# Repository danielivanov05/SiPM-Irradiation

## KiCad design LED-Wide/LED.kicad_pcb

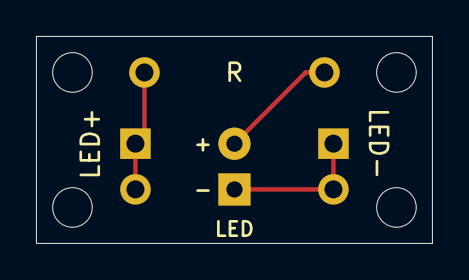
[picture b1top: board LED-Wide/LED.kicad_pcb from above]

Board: 2 copper layers, 22.0 x 11.5 mm, 4 parts (0 on the bottom side), 3 nets.

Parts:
LED: LED; LED_D5.0mm
LED+: Conn_01x02_Pin; PinHeader_1x02_P2.54mm_Vertical
LED-: Conn_01x02_Pin; PinHeader_1x02_P2.54mm_Vertical
R: R; Custom_PinHeader_1x02_P2.54mm_Vertical_Spaced_10mm

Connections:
LED+: LED+.1, LED+.2, R.1
LED-: LED.1 (K), LED-.1, LED-.2
unnamed: LED.2 (A), R.2

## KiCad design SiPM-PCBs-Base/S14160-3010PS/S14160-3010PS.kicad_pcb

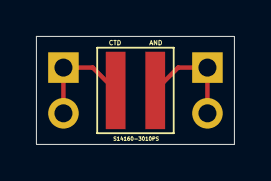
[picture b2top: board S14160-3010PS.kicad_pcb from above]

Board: 2 copper layers, 11.0 x 6.0 mm, 3 parts (0 on the bottom side), 2 nets.

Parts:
D1: S14160-3010PS
J-PWR-2: Conn_01x02_Pin; Custom_PinHeader_1x02_P2.54mm_Vertical
J-SIG-2: Conn_01x02_Pin; Custom_PinHeader_1x02_P2.54mm_Vertical

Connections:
HV+: D1.1 (K-), J-PWR-2.1, J-PWR-2.2
SIG: D1.2 (A+), J-SIG-2.1, J-SIG-2.2

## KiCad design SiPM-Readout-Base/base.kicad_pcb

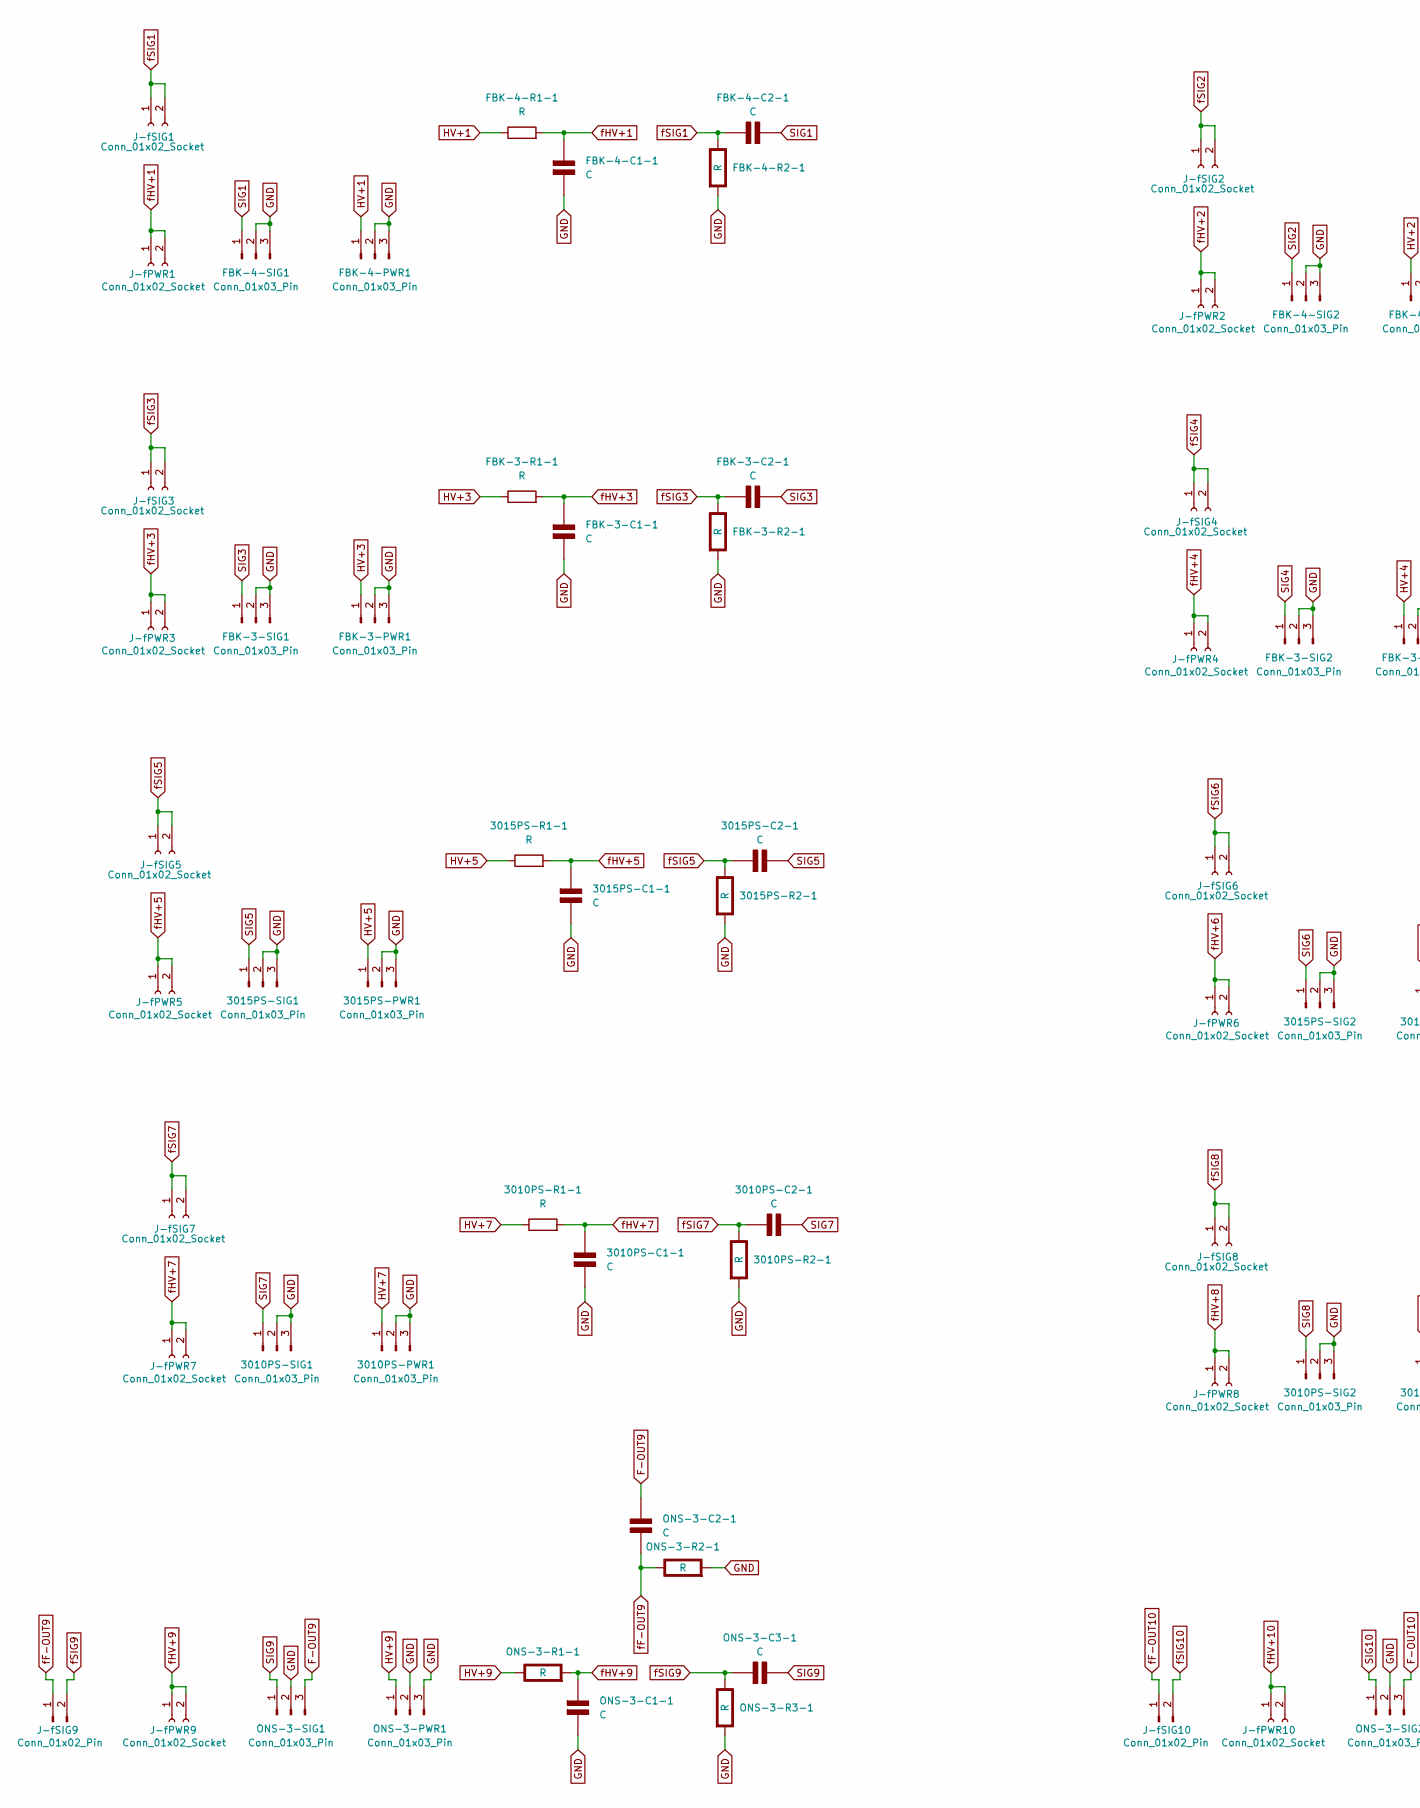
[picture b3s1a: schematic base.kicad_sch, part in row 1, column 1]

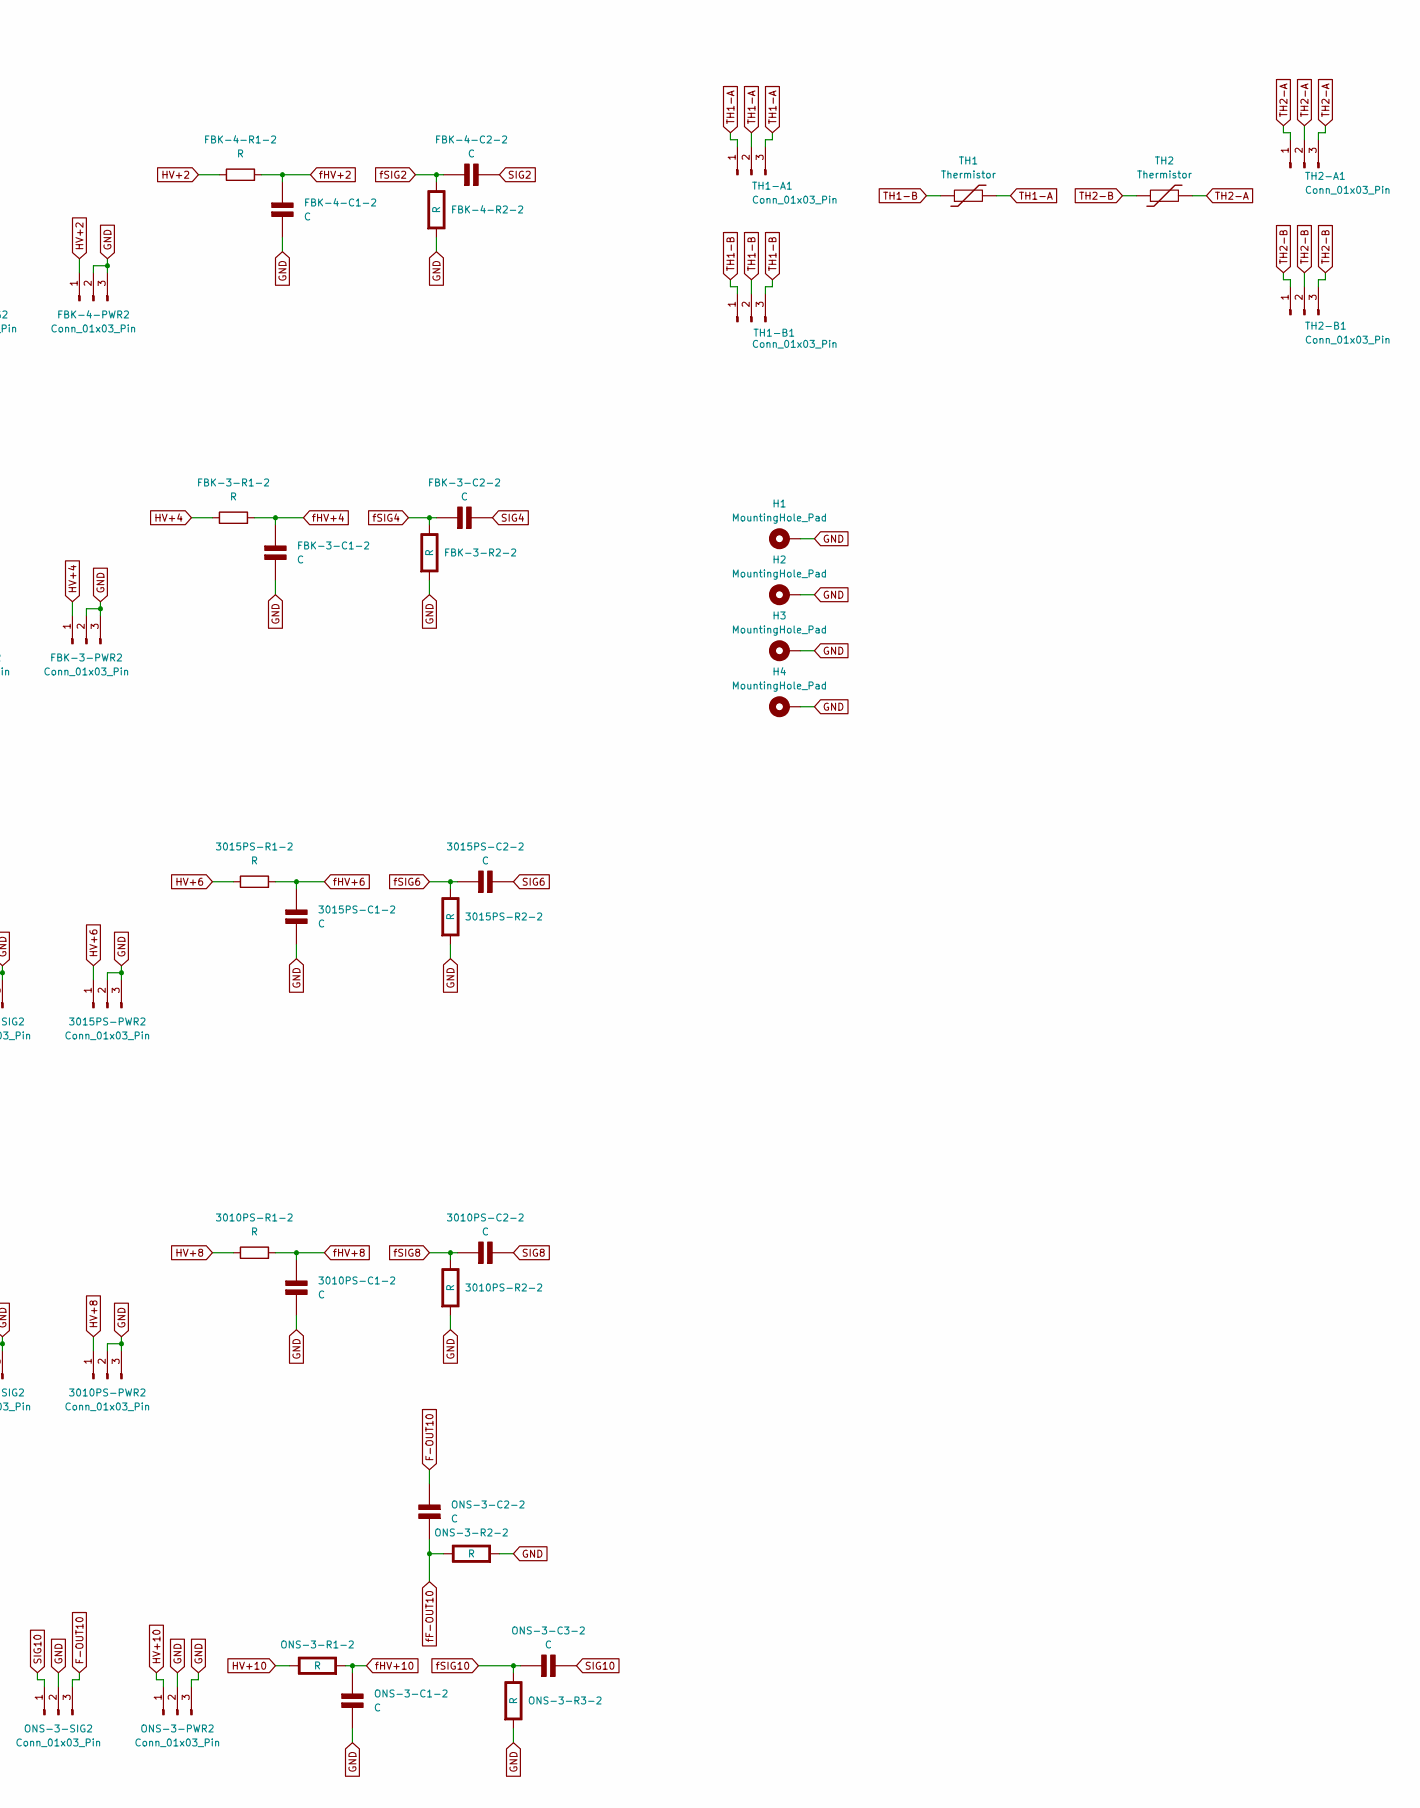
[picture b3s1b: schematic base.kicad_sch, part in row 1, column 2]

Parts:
3010PS-C1-1, 3010PS-C1-2, 3010PS-C2-1, 3010PS-C2-2, 3015PS-C1-1, 3015PS-C1-2, 3015PS-C2-1, 3015PS-C2-2: C; Custom_PinHeader_1x02_P2.54mm_Vertical_Spaced_10mm; Rating V
3010PS-PWR1, 3010PS-PWR2, 3010PS-SIG1, 3010PS-SIG2, 3015PS-PWR1, 3015PS-PWR2, 3015PS-SIG1, 3015PS-SIG2: Conn_01x03_Pin; PinHeader_1x03_P2.54mm_Vertical
3010PS-R1-1, 3010PS-R1-2, 3015PS-R1-1, 3015PS-R1-2: R; Custom_PinHeader_1x02_P2.54mm_Vertical_Spaced_10mm; Rating V
3010PS-R2-1, 3010PS-R2-2, 3015PS-R2-1, 3015PS-R2-2: R; Custom_PinHeader_1x02_P2.54mm_Vertical_Spaced_10mm; Rating W
FBK-3-C1-1, FBK-3-C1-2, FBK-3-C2-1, FBK-3-C2-2, FBK-4-C1-1, FBK-4-C1-2, FBK-4-C2-1, FBK-4-C2-2: C; Custom_PinHeader_1x02_P2.54mm_Vertical_Spaced_10mm; Rating V
FBK-3-PWR1, FBK-3-PWR2, FBK-3-SIG1, FBK-3-SIG2, FBK-4-PWR1, FBK-4-PWR2, FBK-4-SIG1, FBK-4-SIG2: Conn_01x03_Pin; PinHeader_1x03_P2.54mm_Vertical
FBK-3-R1-1, FBK-3-R1-2, FBK-4-R1-1, FBK-4-R1-2: R; Custom_PinHeader_1x02_P2.54mm_Vertical_Spaced_10mm; Rating V
FBK-3-R2-1, FBK-3-R2-2, FBK-4-R2-1, FBK-4-R2-2: R; Custom_PinHeader_1x02_P2.54mm_Vertical_Spaced_10mm; Rating W
H1, H2, H3, H4: MountingHole_Pad; MountingHole_2.2mm_M2_DIN965_Pad_TopBottom
J-fPWR1, J-fPWR2, J-fPWR3, J-fPWR4, J-fPWR5, J-fPWR6, J-fPWR7, J-fPWR8, J-fPWR9, J-fPWR10: Conn_01x02_Socket; Custom_PCB-Sized_PinSocket_1x02_P2.54mm_Vertical
J-fSIG1, J-fSIG2, J-fSIG3, J-fSIG4, J-fSIG5, J-fSIG6, J-fSIG7, J-fSIG8: Conn_01x02_Socket; No_Courtyard_PinSocket_1x02_P2.54mm_Vertical
J-fSIG9, J-fSIG10: Conn_01x02_Pin; No_Courtyard_PinSocket_1x02_P2.54mm_Vertical
ONS-3-C1-1, ONS-3-C1-2, ONS-3-C2-1, ONS-3-C2-2, ONS-3-C3-1, ONS-3-C3-2: C; Custom_PinHeader_1x02_P2.54mm_Vertical_Spaced_10mm; Rating V
ONS-3-PWR1, ONS-3-PWR2, ONS-3-SIG1, ONS-3-SIG2: Conn_01x03_Pin; PinHeader_1x03_P2.54mm_Vertical
ONS-3-R1-1, ONS-3-R1-2, ONS-3-R2-1, ONS-3-R2-2, ONS-3-R3-1, ONS-3-R3-2: R; Custom_PinHeader_1x02_P2.54mm_Vertical_Spaced_10mm; Rating W
TH1, TH2: Thermistor; Custom_PinHeader_1x02_P2.54mm_Vertical_Spaced_10mm
TH1-A1, TH1-B1, TH2-A1, TH2-B1: Conn_01x03_Pin; PinHeader_1x03_P2.54mm_Vertical

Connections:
F-OUT9: ONS-3-C2-1.2 (-), ONS-3-SIG1.3
F-OUT10: ONS-3-C2-2.2 (-), ONS-3-SIG2.3
GND: 3010PS-C1-1.2 (-), 3010PS-C1-2.2 (-), 3010PS-PWR1.2, 3010PS-PWR1.3, 3010PS-PWR2.2, 3010PS-PWR2.3, 3010PS-R2-1.2 (-), 3010PS-R2-2.2 (-), 3010PS-SIG1.2, 3010PS-SIG1.3, 3010PS-SIG2.2, 3010PS-SIG2.3, 3015PS-C1-1.2 (-), 3015PS-C1-2.2 (-), 3015PS-PWR1.2, 3015PS-PWR1.3, 3015PS-PWR2.2, 3015PS-PWR2.3, 3015PS-R2-1.2 (-), 3015PS-R2-2.2 (-), 3015PS-SIG1.2, 3015PS-SIG1.3, 3015PS-SIG2.2, 3015PS-SIG2.3, FBK-3-C1-1.2 (-), FBK-3-C1-2.2 (-), FBK-3-PWR1.2, FBK-3-PWR1.3, FBK-3-PWR2.2, FBK-3-PWR2.3, FBK-3-R2-1.2 (-), FBK-3-R2-2.2 (-), FBK-3-SIG1.2, FBK-3-SIG1.3, FBK-3-SIG2.2, FBK-3-SIG2.3, FBK-4-C1-1.2 (-), FBK-4-C1-2.2 (-), FBK-4-PWR1.2, FBK-4-PWR1.3, FBK-4-PWR2.2, FBK-4-PWR2.3, FBK-4-R2-1.2 (-), FBK-4-R2-2.2 (-), FBK-4-SIG1.2, FBK-4-SIG1.3, FBK-4-SIG2.2, FBK-4-SIG2.3, H1.1, H2.1, H3.1, H4.1, ONS-3-C1-1.2 (-), ONS-3-C1-2.2 (-), ONS-3-PWR1.2, ONS-3-PWR1.3, ONS-3-PWR2.2, ONS-3-PWR2.3, ONS-3-R2-1.2 (-), ONS-3-R2-2.2 (-), ONS-3-R3-1.2 (-), ONS-3-R3-2.2 (-), ONS-3-SIG1.2, ONS-3-SIG2.2
HV+1: FBK-4-PWR1.1, FBK-4-R1-1.1
HV+2: FBK-4-PWR2.1, FBK-4-R1-2.1
HV+3: FBK-3-PWR1.1, FBK-3-R1-1.1
HV+4: FBK-3-PWR2.1, FBK-3-R1-2.1
HV+5: 3015PS-PWR1.1, 3015PS-R1-1.1
HV+6: 3015PS-PWR2.1, 3015PS-R1-2.1
HV+7: 3010PS-PWR1.1, 3010PS-R1-1.1
HV+8: 3010PS-PWR2.1, 3010PS-R1-2.1
HV+9: ONS-3-PWR1.1, ONS-3-R1-1.1 (+)
HV+10: ONS-3-PWR2.1, ONS-3-R1-2.1 (+)
SIG1: FBK-4-C2-1.2 (-), FBK-4-SIG1.1
SIG2: FBK-4-C2-2.2 (-), FBK-4-SIG2.1
SIG3: FBK-3-C2-1.2 (-), FBK-3-SIG1.1
SIG4: FBK-3-C2-2.2 (-), FBK-3-SIG2.1
SIG5: 3015PS-C2-1.2 (-), 3015PS-SIG1.1
SIG6: 3015PS-C2-2.2 (-), 3015PS-SIG2.1
SIG7: 3010PS-C2-1.2 (-), 3010PS-SIG1.1
SIG8: 3010PS-C2-2.2 (-), 3010PS-SIG2.1
SIG9: ONS-3-C3-1.2 (-), ONS-3-SIG1.1
SIG10: ONS-3-C3-2.2 (-), ONS-3-SIG2.1
TH1-A: TH1.2, TH1-A1.1, TH1-A1.2, TH1-A1.3
TH1-B: TH1.1, TH1-B1.1, TH1-B1.2, TH1-B1.3
TH2-A: TH2.2, TH2-A1.1, TH2-A1.2, TH2-A1.3
TH2-B: TH2.1, TH2-B1.1, TH2-B1.2, TH2-B1.3
fF-OUT9: J-fSIG9.1, ONS-3-C2-1.1 (+), ONS-3-R2-1.1 (+)
fF-OUT10: J-fSIG10.1, ONS-3-C2-2.1 (+), ONS-3-R2-2.1 (+)
fHV+1: FBK-4-C1-1.1 (+), FBK-4-R1-1.2, J-fPWR1.1, J-fPWR1.2
fHV+2: FBK-4-C1-2.1 (+), FBK-4-R1-2.2, J-fPWR2.1, J-fPWR2.2
fHV+3: FBK-3-C1-1.1 (+), FBK-3-R1-1.2, J-fPWR3.1, J-fPWR3.2
fHV+4: FBK-3-C1-2.1 (+), FBK-3-R1-2.2, J-fPWR4.1, J-fPWR4.2
fHV+5: 3015PS-C1-1.1 (+), 3015PS-R1-1.2, J-fPWR5.1, J-fPWR5.2
fHV+6: 3015PS-C1-2.1 (+), 3015PS-R1-2.2, J-fPWR6.1, J-fPWR6.2
fHV+7: 3010PS-C1-1.1 (+), 3010PS-R1-1.2, J-fPWR7.1, J-fPWR7.2
fHV+8: 3010PS-C1-2.1 (+), 3010PS-R1-2.2, J-fPWR8.1, J-fPWR8.2
fHV+9: J-fPWR9.1, J-fPWR9.2, ONS-3-C1-1.1 (+), ONS-3-R1-1.2 (-)
fHV+10: J-fPWR10.1, J-fPWR10.2, ONS-3-C1-2.1 (+), ONS-3-R1-2.2 (-)
fSIG1: FBK-4-C2-1.1 (+), FBK-4-R2-1.1 (+), J-fSIG1.1, J-fSIG1.2
fSIG2: FBK-4-C2-2.1 (+), FBK-4-R2-2.1 (+), J-fSIG2.1, J-fSIG2.2
fSIG3: FBK-3-C2-1.1 (+), FBK-3-R2-1.1 (+), J-fSIG3.1, J-fSIG3.2
fSIG4: FBK-3-C2-2.1 (+), FBK-3-R2-2.1 (+), J-fSIG4.1, J-fSIG4.2
fSIG5: 3015PS-C2-1.1 (+), 3015PS-R2-1.1 (+), J-fSIG5.1, J-fSIG5.2
fSIG6: 3015PS-C2-2.1 (+), 3015PS-R2-2.1 (+), J-fSIG6.1, J-fSIG6.2
fSIG7: 3010PS-C2-1.1 (+), 3010PS-R2-1.1 (+), J-fSIG7.1, J-fSIG7.2
fSIG8: 3010PS-C2-2.1 (+), 3010PS-R2-2.1 (+), J-fSIG8.1, J-fSIG8.2
fSIG9: J-fSIG9.2, ONS-3-C3-1.1 (+), ONS-3-R3-1.1 (+)
fSIG10: J-fSIG10.2, ONS-3-C3-2.1 (+), ONS-3-R3-2.1 (+)

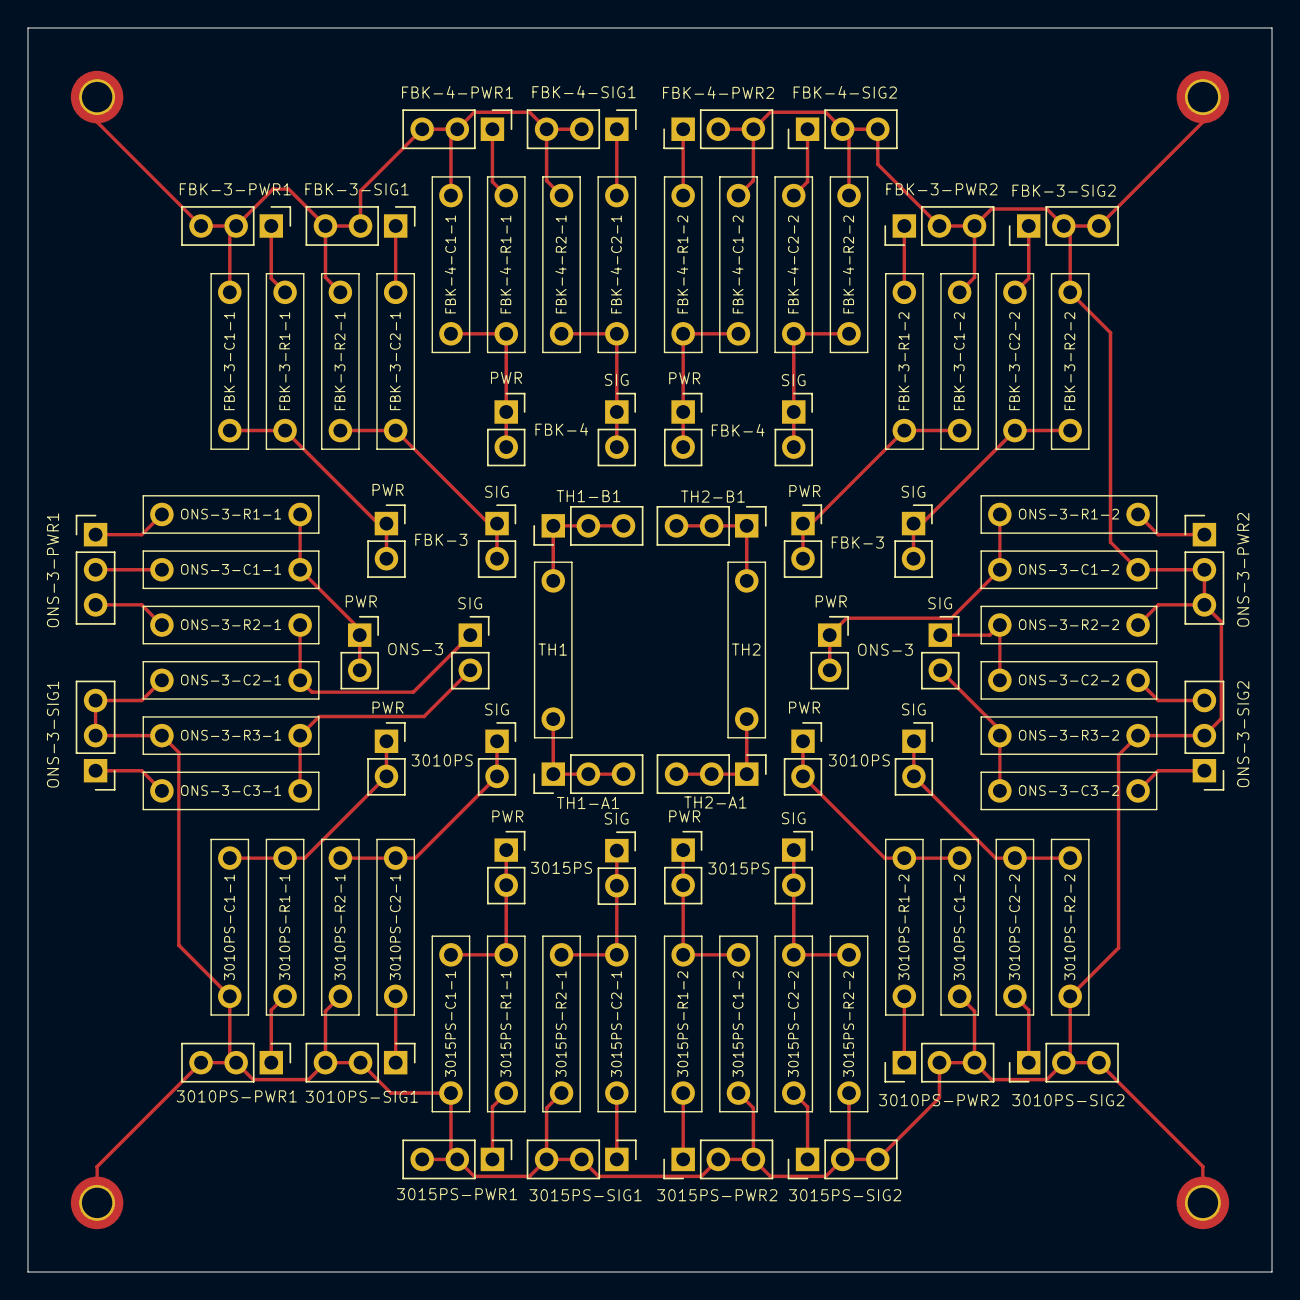
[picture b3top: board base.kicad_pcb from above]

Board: 2 copper layers, 90.0 x 90.0 mm, 94 parts (0 on the bottom side), 49 nets.

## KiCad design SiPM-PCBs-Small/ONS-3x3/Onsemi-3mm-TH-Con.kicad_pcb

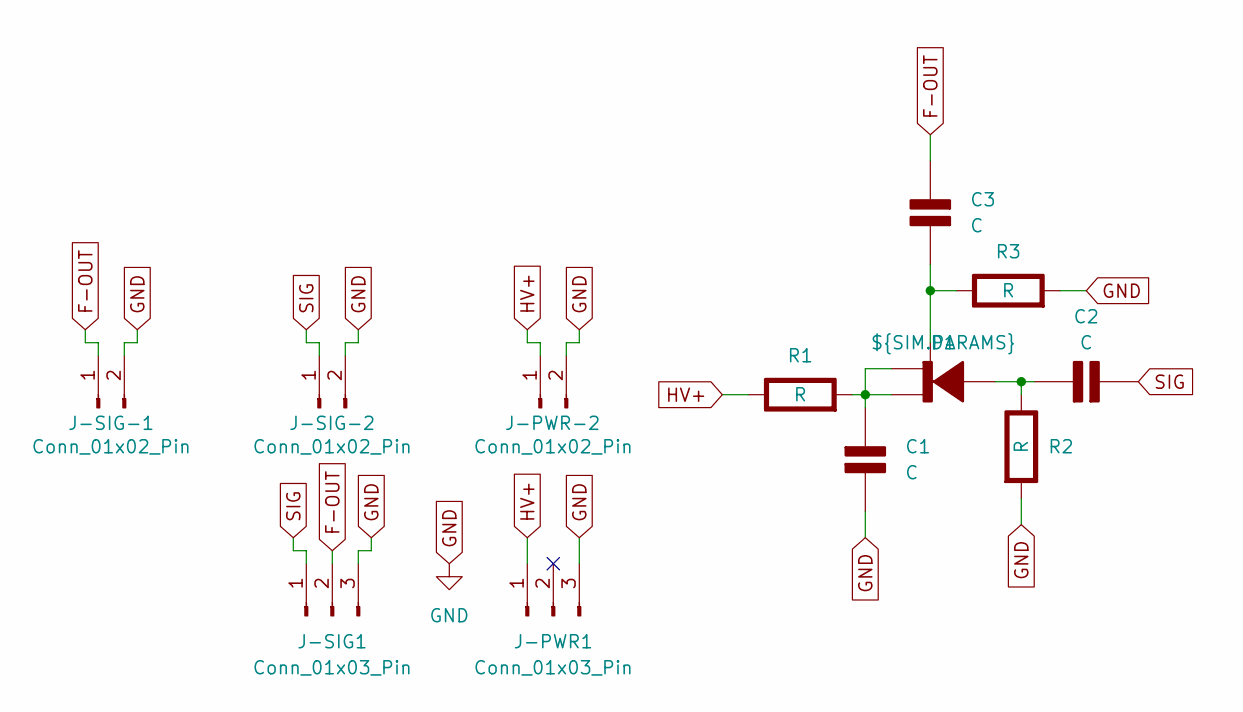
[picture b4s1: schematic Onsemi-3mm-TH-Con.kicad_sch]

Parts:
C1, C2: C; PinHeader_1x04_P2.54mm_Vertical_Spaced; Rating V
C3: C; PinHeader_1x04_P2.54mm_Vertical_Spaced_Mini; Rating V
D1: ${SIM.PARAMS}; ONS-MICROFJ-30050; Rating V/A
J-PWR1: Conn_01x03_Pin; PinHeader_1x03_P2.54mm_Vertical
J-PWR-2: Conn_01x02_Pin; MMCX_Molex_73415-1471_Vertical
J-SIG1: Conn_01x03_Pin; PinHeader_1x03_P2.54mm_Vertical
J-SIG-1, J-SIG-2: Conn_01x02_Pin; MMCX_Molex_73415-1471_Vertical
R1, R2: R; PinHeader_1x04_P2.54mm_Vertical_Spaced; Rating W
R3: R; PinHeader_1x04_P2.54mm_Vertical_Spaced_Mini; Rating W

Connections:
F-OUT: C3.2 (-), J-SIG1.2, J-SIG-1.1
GND: C1.2 (-), J-PWR1.3, J-PWR-2.2, J-SIG1.3, J-SIG-1.2, J-SIG-2.2, R2.2 (-), R3.2 (-)
HV+: J-PWR1.1, J-PWR-2.1, R1.1 (+)
unnamed: C1.1 (+), D1.A1 (K-), D1.C3 (K-), R1.2 (-)
unnamed: C2.1 (+), D1.B1 (A+), R2.1 (+)
unnamed: C3.1 (+), D1.B3 (A2+), R3.1 (+)
SIG: C2.2 (-), J-SIG1.1, J-SIG-2.1

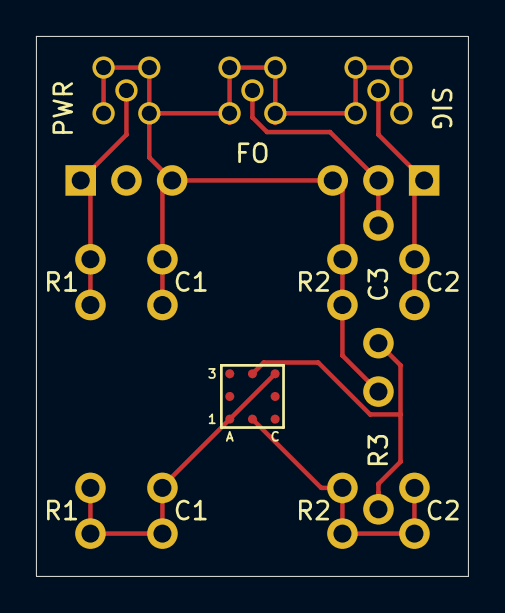
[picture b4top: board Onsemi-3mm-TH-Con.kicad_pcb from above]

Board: 2 copper layers, 24.0 x 30.0 mm, 12 parts (0 on the bottom side), 7 nets.

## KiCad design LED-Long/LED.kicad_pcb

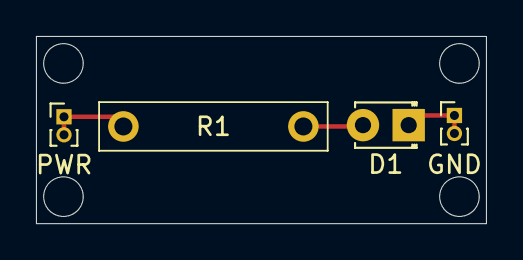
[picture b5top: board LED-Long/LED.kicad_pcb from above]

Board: 2 copper layers, 25.0 x 10.4 mm, 4 parts (0 on the bottom side), 3 nets.

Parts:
D1: LED; LED_D1.8mm_W3.3mm_H2.4mm
GND: Conn_01x02_Pin; PinHeader_1x02_P1.00mm_Vertical
PWR: Conn_01x02_Pin; PinHeader_1x02_P1.00mm_Vertical
R1: R; Custom_PinHeader_1x02_P2.54mm_Vertical_Spaced_10mm

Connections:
GND: D1.1 (K), GND.1, GND.2
unnamed: D1.2 (A), R1.2
PWR: PWR.1, PWR.2, R1.1

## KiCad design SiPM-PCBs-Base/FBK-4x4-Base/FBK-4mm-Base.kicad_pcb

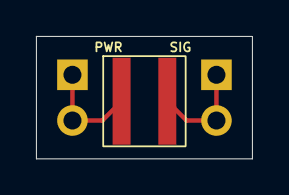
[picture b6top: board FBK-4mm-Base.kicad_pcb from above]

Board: 2 copper layers, 12.0 x 6.8 mm, 3 parts (0 on the bottom side), 2 nets.

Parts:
D1: ASD-RGB4S-P-40
J-SIG-1, J-SIG-2: Conn_01x02_Pin; PinHeader_1x02_P2.54mm_Vertical

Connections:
HV+: D1.1 (K-), J-SIG-2.1, J-SIG-2.2
SIG: D1.2 (A+), J-SIG-1.1, J-SIG-1.2

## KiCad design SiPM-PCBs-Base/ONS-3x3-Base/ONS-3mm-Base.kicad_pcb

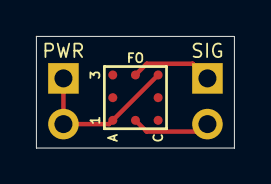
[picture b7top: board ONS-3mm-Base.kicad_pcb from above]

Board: 2 copper layers, 11.0 x 6.2 mm, 3 parts (0 on the bottom side), 3 nets.

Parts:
D1: ONS-MICROFJ-30050
J-PWR-1: Conn_01x02_Pin; PinHeader_1x02_P2.54mm_Vertical
J-SIG-1: Conn_01x02_Pin; PinHeader_1x02_P2.54mm_Vertical

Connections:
F-OUT: D1.B3 (A2+), J-SIG-1.1
HV+: D1.A1 (K-), D1.C3 (K-), J-PWR-1.1, J-PWR-1.2
SIG: D1.B1 (A+), J-SIG-1.2

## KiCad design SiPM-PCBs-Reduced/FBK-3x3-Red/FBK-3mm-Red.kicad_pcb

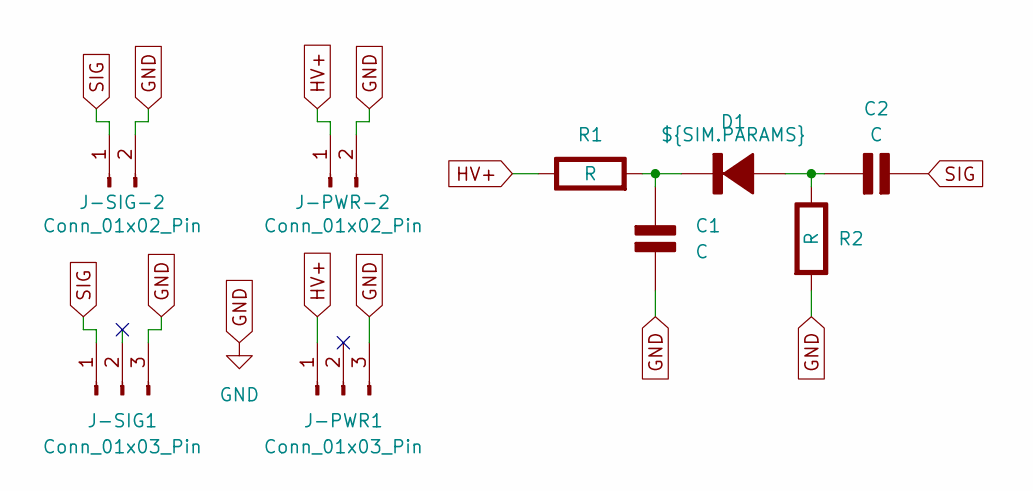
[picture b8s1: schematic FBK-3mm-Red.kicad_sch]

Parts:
C1, C2: C; PinHeader_1x04_P2.54mm_Vertical_Spaced_Mini; Rating V
D1: ${SIM.PARAMS}; ASD-RGB3S-P-40; Rating V/A
J-PWR1: Conn_01x03_Pin; PinHeader_1x03_P2.54mm_Vertical
J-PWR-2: Conn_01x02_Pin; MMCX_Molex_73415-1471_Vertical
J-SIG1: Conn_01x03_Pin; PinHeader_1x03_P2.54mm_Vertical
J-SIG-2: Conn_01x02_Pin; MMCX_Molex_73415-1471_Vertical
R1, R2: R; PinHeader_1x04_P2.54mm_Vertical_Spaced_Mini; Rating W

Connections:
GND: C1.2 (-), J-PWR1.3, J-PWR-2.2, J-SIG1.3, J-SIG-2.2, R2.2 (-)
HV+: J-PWR1.1, J-PWR-2.1, R1.1 (+)
unnamed: C1.1 (+), D1.1 (K-), R1.2 (-)
unnamed: C2.1 (+), D1.2 (A+), R2.1 (+)
SIG: C2.2 (-), J-SIG1.1, J-SIG-2.1

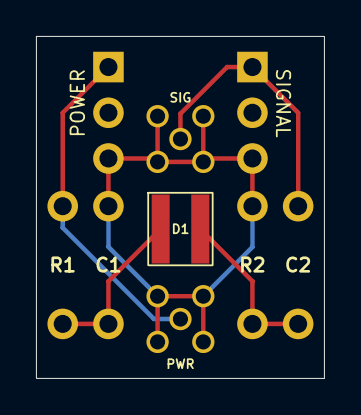
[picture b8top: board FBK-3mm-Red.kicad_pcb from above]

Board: 2 copper layers, 16.0 x 19.0 mm, 9 parts (0 on the bottom side), 5 nets.

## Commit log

2025-09-25 Box design and LED PCB alignment changes
2025-09-25 added tracks to LED-Wide PCB
2025-09-26 Box redesign
2025-09-30 Redesigned LED-Wide PCB; created Fabrication files; added template for fabrication order request; added final order contents.
2025-09-30 Deleting a couple of unneeded files.
2025-10-10 Added new version of Box. Reduced size due to printing constraints. Connector cutouts remade to match connector shape.
2025-10-16 Created bolt and nut for board attachment; redesigned box and lid (thinner walls + cantelever snap fit)
2025-10-16 Lid changed to L-shape with rails and one snapfit lever
2025-10-16 Edited box to fit the new lid. Snap Fit hole not made.
2025-10-16 Added snapfit cutout for box and updated assembly
2025-10-16 Box and lid tolerances added. Lid is lit, fr fr.
2025-10-17 Small box fix. Added BambuLab files and STEP files for current design.
2025-11-05 Partial redesign of the Box. For completion.
2025-11-05 dani e gey
